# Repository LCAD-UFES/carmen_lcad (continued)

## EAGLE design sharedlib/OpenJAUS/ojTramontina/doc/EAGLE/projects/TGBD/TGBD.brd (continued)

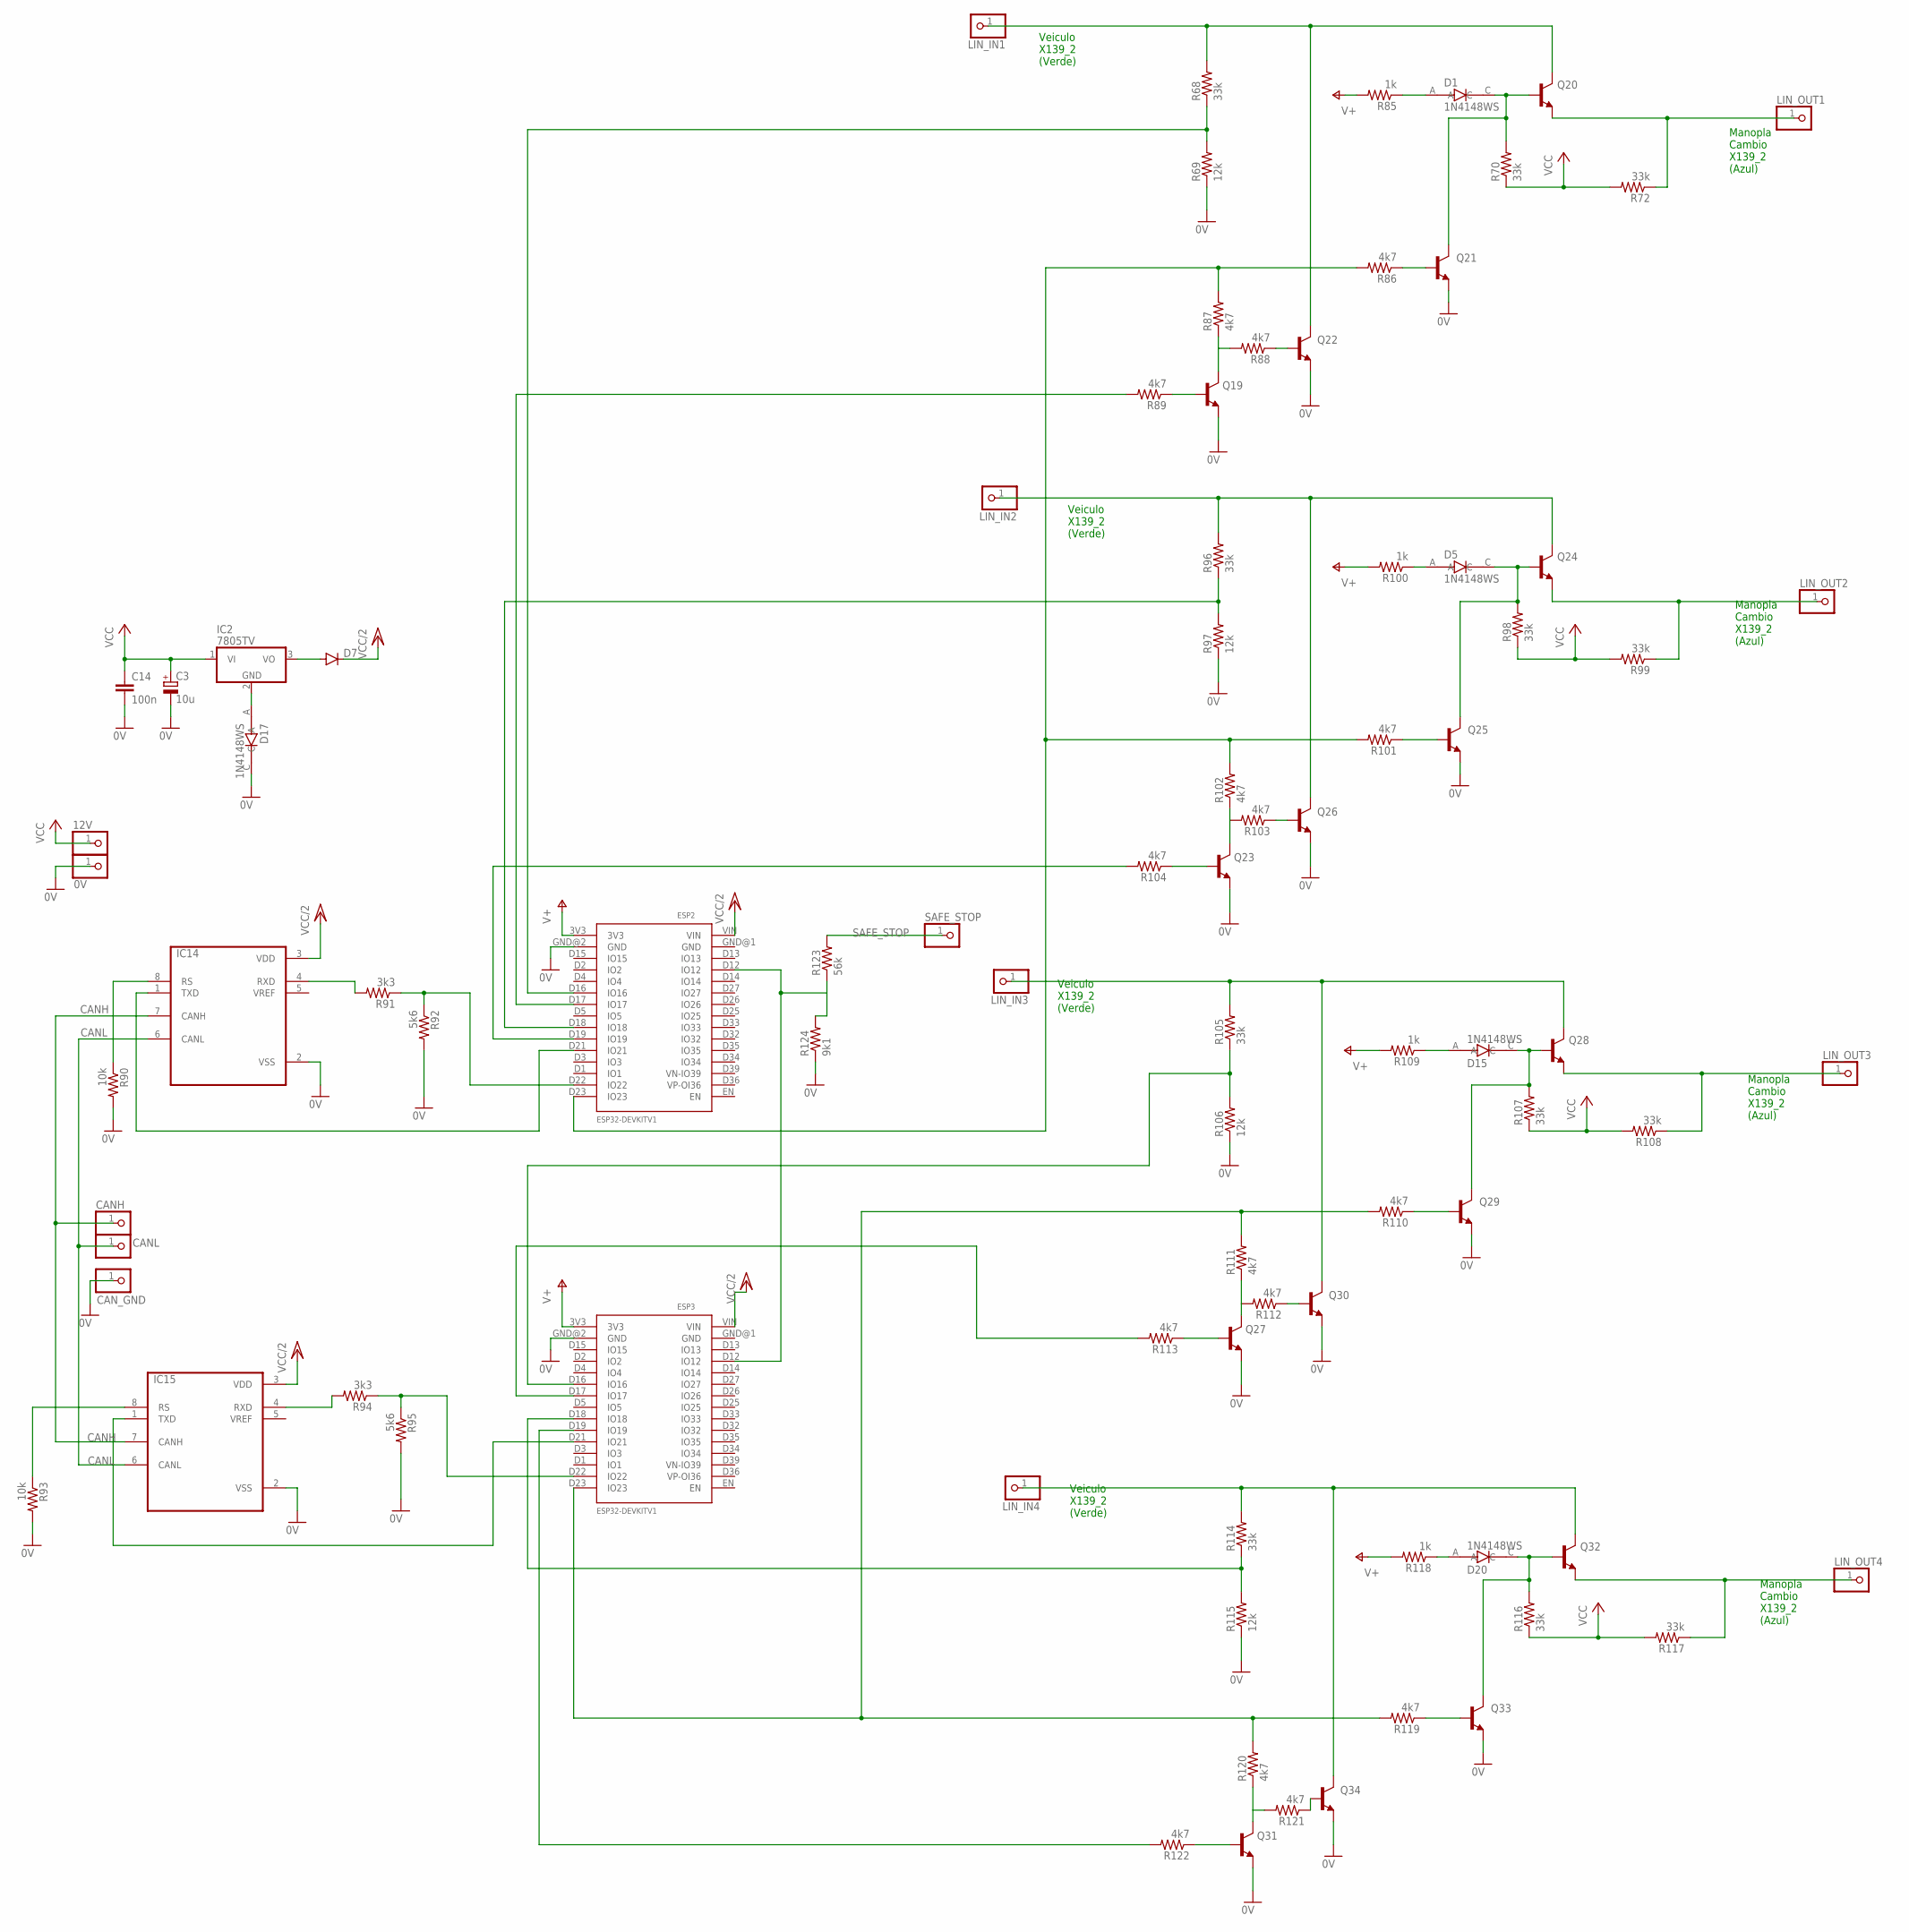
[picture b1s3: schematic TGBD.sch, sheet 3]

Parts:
0V, 12V: PINHD-1X1; 1X01
C3: 10u; A/3216-18R
C14: 100n; C0402
CANH: PINHD-1X1; 1X01
CANL: PINHD-1X1; 1X01
CAN_GND: PINHD-1X1; 1X01
D1, D5, D15, D17, D20: 1N4148WS; SODFL2512X100N
D7: DIODE-SOD123; SOD123
ESP2, ESP3: ESP32DEVKITV1; ESP32-DEVKITV1
IC2: 7805TV; TO220V
IC14, IC15: MCP2551-I/SN; SOIC127P599X175-8N
LIN_IN1, LIN_IN2, LIN_IN3, LIN_IN4: PINHD-1X1; 1X01
LIN_OUT1, LIN_OUT2, LIN_OUT3, LIN_OUT4: PINHD-1X1; 1X01
Q19, Q20, Q21, Q22, Q23, Q24, Q25, Q26, Q27, Q28, Q29, Q30, Q31, Q32, Q33, Q34: -NPN-TO92; TO92
R68, R70, R72, R96, R98, R99, R105, R107, R108, R114, R116, R117: 33k; R0402
R69, R97, R106, R115: 12k; R0603
R85, R100, R109, R118: 1k; R0402
R86, R87, R88, R89, R101, R102, R103, R104, R110, R111, R112, R113, R119, R120, R121, R122: 4k7; R0402
R90, R93: 10k; R0603
R91, R94: 3k3; R0402
R92, R95: 5k6; R0603
R123: 56k; R0603
R124: 9k1; R0603
SAFE_STOP: PINHD-1X1; 1X01

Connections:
0V: 0V.1, C3.-, C14.2, CAN_GND.1, D17.C, ESP2.GND@2 (GND), ESP3.GND@2 (GND), IC14.2 (VSS), IC15.2 (VSS), Q19.1 (E), Q21.1 (E), Q22.1 (E), Q23.1 (E), Q25.1 (E), Q26.1 (E), Q27.1 (E), Q29.1 (E), Q30.1 (E), Q31.1 (E), Q33.1 (E), Q34.1 (E), R69.1, R90.2, R92.2, R93.2, R95.2, R97.1, R106.1, R115.1, R124.1
CANH: CANH.1, IC14.7 (CANH), IC15.7 (CANH)
CANL: CANL.1, IC14.6 (CANL), IC15.6 (CANL)
unnamed: D1.C, Q20.2 (B), Q21.3 (C), R70.2
unnamed: D20.A, R118.1
unnamed: Q21.2 (B), R86.1
unnamed: Q19.3 (C), R87.1, R88.2
unnamed: Q22.2 (B), R88.1
unnamed: Q19.2 (B), R89.1
unnamed: D17.A, IC2.2 (GND)
unnamed: D7.A, IC2.3 (VO)
unnamed: IC14.8 (RS), R90.1
unnamed: IC14.4 (RXD), R91.2
unnamed: IC15.8 (RS), R93.1
unnamed: D15.A, R109.1
unnamed: D5.C, Q24.2 (B), Q25.3 (C), R98.2
unnamed: D5.A, R100.1
unnamed: Q25.2 (B), R101.1
unnamed: Q23.3 (C), R102.1, R103.2
unnamed: Q26.2 (B), R103.1
unnamed: Q23.2 (B), R104.1
unnamed: D15.C, Q28.2 (B), Q29.3 (C), R107.2
unnamed: D1.A, R85.1
unnamed: Q29.2 (B), R110.1
unnamed: Q27.3 (C), R111.1, R112.2
unnamed: Q30.2 (B), R112.1
unnamed: Q27.2 (B), R113.1
unnamed: LIN_OUT1.1, Q20.1 (E), R72.1
unnamed: LIN_OUT3.1, Q28.1 (E), R108.1
unnamed: D20.C, Q32.2 (B), Q33.3 (C), R116.2
unnamed: ESP2.D16 (IO16), R68.1, R69.2
unnamed: Q33.2 (B), R119.1
unnamed: Q31.3 (C), R120.1, R121.2
unnamed: Q34.2 (B), R121.1
unnamed: Q31.2 (B), R122.1
unnamed: LIN_OUT2.1, Q24.1 (E), R99.1
unnamed: ESP2.D12 (IO12), ESP3.D12 (IO12), R123.1, R124.2
unnamed: IC15.4 (RXD), R94.2
unnamed: ESP2.D17 (IO17), R89.2
unnamed: ESP2.D18 (IO18), R96.1, R97.2
unnamed: ESP2.D19 (IO19), R104.2
unnamed: ESP3.D16 (IO16), R105.1, R106.2
unnamed: ESP3.D17 (IO17), R113.2
unnamed: ESP3.D18 (IO18), R114.1, R115.2
unnamed: ESP3.D19 (IO19), R122.2
unnamed: LIN_OUT4.1, Q32.1 (E), R117.1
unnamed: ESP2.D22 (IO22), R91.1, R92.1
unnamed: ESP2.D23 (IO23), R86.2, R87.2, R101.2, R102.2
unnamed: ESP3.D23 (IO23), R110.2, R111.2, R119.2, R120.2
unnamed: ESP2.D21 (IO21), IC14.1 (TXD)
unnamed: ESP3.D22 (IO22), R94.1, R95.1
unnamed: ESP3.D21 (IO21), IC15.1 (TXD)
unnamed: LIN_IN1.1, Q20.3 (C), Q22.3 (C), R68.2
unnamed: LIN_IN2.1, Q24.3 (C), Q26.3 (C), R96.2
unnamed: LIN_IN3.1, Q28.3 (C), Q30.3 (C), R105.2
unnamed: LIN_IN4.1, Q32.3 (C), Q34.3 (C), R114.2
SAFE_STOP: R123.2, SAFE_STOP.1
V+: ESP2.3V3, ESP3.3V3, R85.2, R100.2, R109.2, R118.2; also elsewhere on the board
VCC: 12V.1, C3.+, C14.1, IC2.1 (VI), R70.1, R72.2, R98.1, R99.2, R107.1, R108.2, R116.1, R117.2
VCC/2: D7.C, ESP2.VIN, ESP3.VIN, IC14.3 (VDD), IC15.3 (VDD)

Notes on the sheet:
Manopla Cambio X139_2 (Azul)
Veiculo X139_2 (Verde)

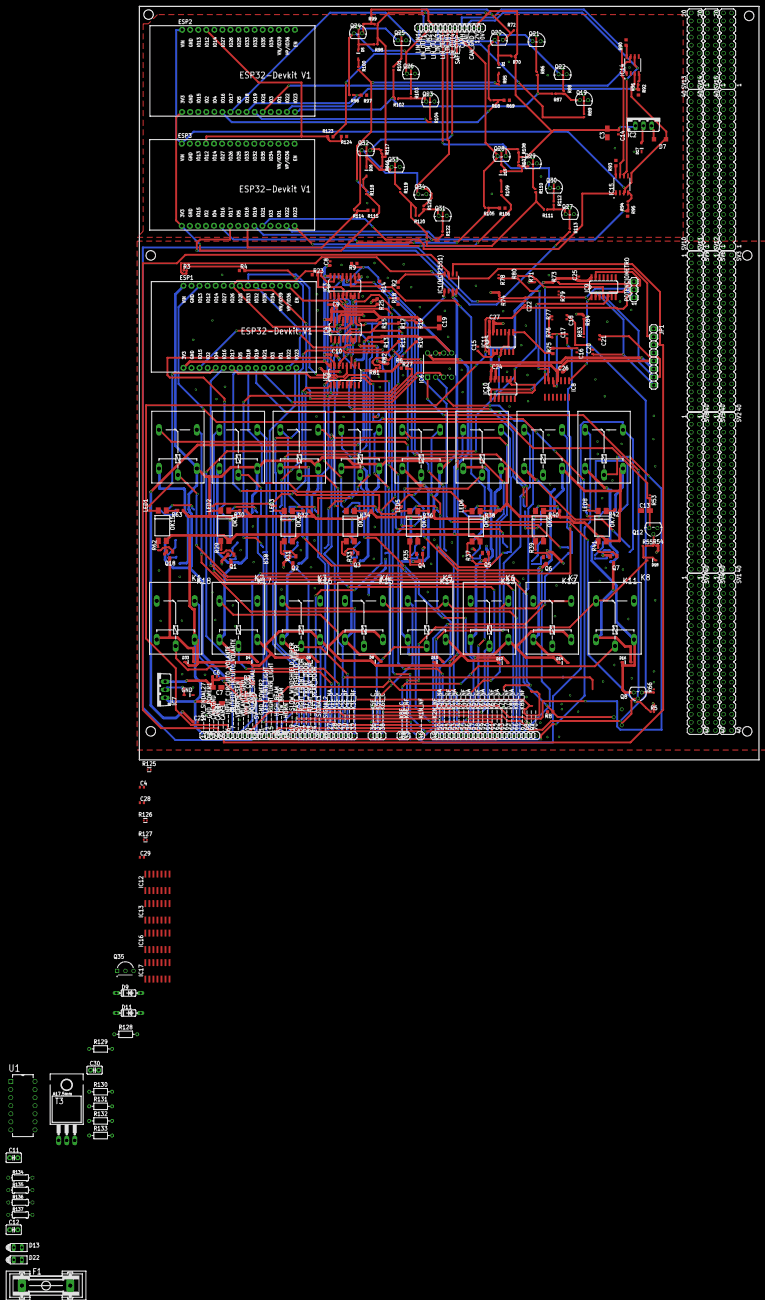
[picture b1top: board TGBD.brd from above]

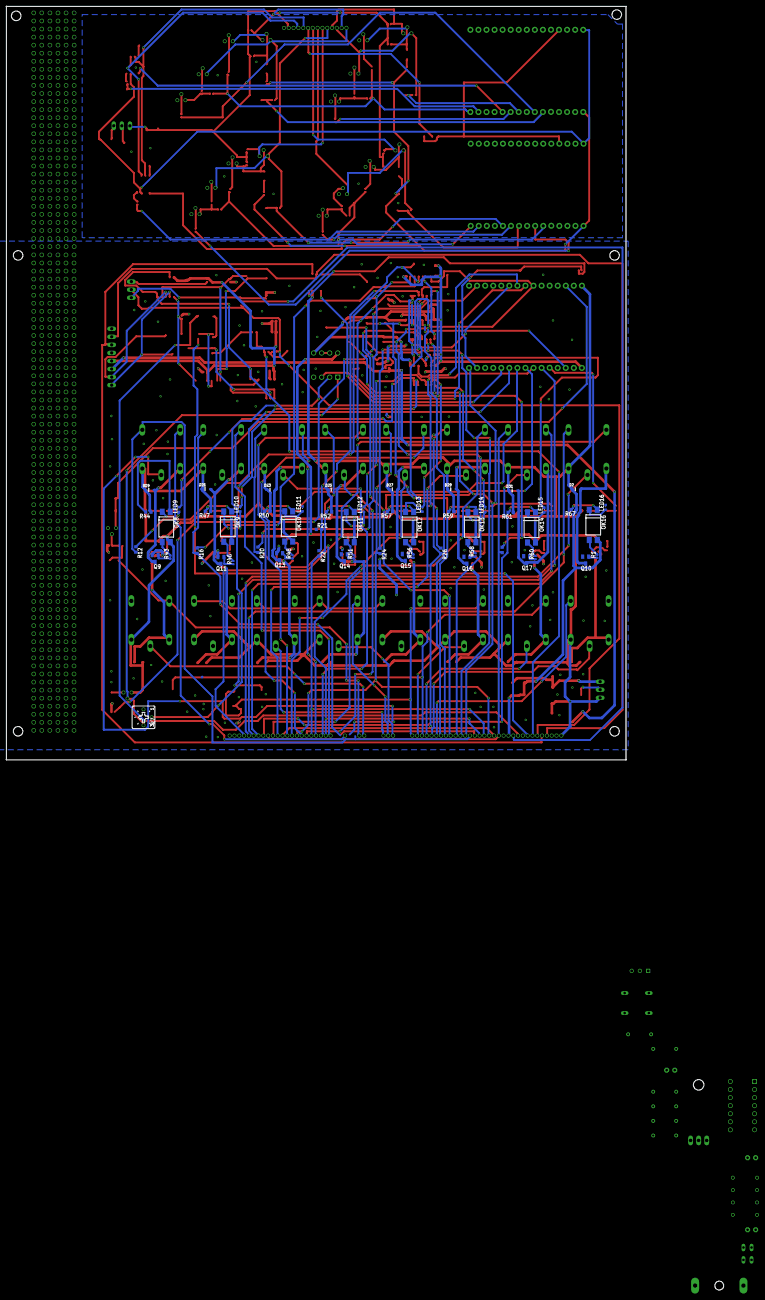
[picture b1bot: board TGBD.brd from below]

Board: 2 copper layers, 195.3 x 237.5 mm, 387 parts (57 on the bottom side), 261 nets.

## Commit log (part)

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2024-07-03 Odometry tests Hercules
2024-07-03 Visualize steering Hercules
2024-07-03 Updating steering visualization Hercules
2024-07-09 Steering Measurement Hercules
2024-07-09 Correcao do codigo de teste de angulo do Hercules
2024-07-09 Lume Mission
2024-07-09 Atualizacao de parametros e process do Hercules
2024-07-11 Adicionando parametros publish_gps
2024-07-11 Adicionando parâmetros publish_gps
2024-07-12 Calibracao de odometria Hercules
2024-07-22 subindo codigo do esp com a build
2024-07-22 removendo a build do esp , e subindo as alteracoes do hercules
2024-07-22 Adicionando controle do Steering Angle via can + build
2024-07-22 adicionando can para o esp
2024-07-25 Atualizacao de Parametros e Controle do Hercules
2024-08-05 PID hercules totalmente proporcional
2024-08-06 adicionando argumento para acionar RVIZ do process
2024-08-14 atulizacao process e missao
2024-08-14 Mensagem do commit
2024-08-19 correcao do codigo do esp
2024-08-19 subindo mudancas no PID atrasadas
2024-08-29 Adicao de funcionalidades para funcionar o Argos com o ojTorc
2024-09-03 subindo mudanças da apresentação
2024-09-04 utilizacao do novo mapa
2024-09-10 tudo pronto para a visita da ArcelorMittal
2024-09-12 Update readme.md - 0.00 meaning no translations
2024-09-12 Update readme.md - 0.00 meaning no rotations
2024-09-12 Argos Lidar initial code
2024-09-12 atualizacao da pose da missao
2024-09-14 melhorias no NMP
2024-09-17 melhorias para a missao de corredor do Hercules
2024-09-18 criacao da missao do corredor
2024-09-18 Argos lidar
2024-09-19 Modificacoes argos_lidar
2024-10-04 Alteracao do task manager e modificacao de parametros
2024-10-04 mission e process usando yolo
2024-10-07 Avanco lidar argos
2024-10-07 Avancos task manager
2024-10-08 Subindo grafo e outras coisas
2024-10-10 Adicao do map_ct13_hercules_lcad4_20240918
2024-10-11 Atualizar posicao caminhao hercules
2024-10-11 Adicionando modificacoes no Argos Lidar
2024-10-14 corrigindo conversao para esférica
2024-10-16 subindo mudancas do argos
2024-10-16 ajustes de parametros
2024-10-16 subindo process
2024-10-16 mudancao no argos playback.ini
2024-10-16 remocao de bug no viewer_3D
2024-10-17 Alterando parametros de Visualizacao Viewer e Argos_lidar do Argos
2024-10-23 renomeando process hercules e mudancas no lidar do argos
2024-10-24 subindo process hercules com nomes novos
2024-10-24 subindo binario do fastslam
2024-10-24 correcao
2024-10-24 adicionando binario correto
2024-10-24 subindo mudancas hercules
2024-10-24 subindo process fastslam argos
2024-10-24 subindo arquivos do argos
2024-10-24 subindo modelo 3d do argos comprimido
2024-10-25 subindo mudancas nos process
2024-10-25 pequenas mudacas process hercules playback
2024-10-25 correcao process argos playback
2024-11-13 mudancas process ct de portas abertas e killros
2024-11-28 consertando process da volta ufes
2024-11-28 comecando a desenvolver o conversor de mapa ROS/Carmen
2024-11-28 teste compilando
2025-01-06 colocando ojTorc para funcionar com webrtc
2025-01-09 pose global do argos funcionando
2025-01-13 configurando process playback webrtc
2025-01-13 argos global pos funcionando
2025-01-22 corrigindo escrita no argos.ini
2025-01-27 envio de odometria para o carmen
2025-01-28 publicando globalpos e trabalho com mapa
2025-02-06 correcao mapa e global_pos
2025-02-12 subindo process argos
2025-02-12 subindo pose global
2025-02-25 criacao ipc_watcher
    descobrindo msgs e subscribers
2025-02-25 subindo ipc_watcher
2025-02-25 inicio mapper
2025-02-25 trabalhando no argos_Ros_mapper
2025-03-06 preprando para mexer no mapper
2025-03-06 subindo correcoes codigo globalpos
2025-03-08 melhorias no modo navigate do Argos
2025-03-10 subindo modelo do go1
2025-03-10 adicao de mecanismos de simulacao do Unitree Go1
2025-03-25 inclusao de codigo no navigator_gui2 para salvar poses.txt para o relatorio para a ArcelorMittal
2025-03-25 codigo commitado que estava no laptop do Argos
2025-03-25 inclusao da versao do LiDAR Ouster do Lcad e ajuste do process argos/process-argos-lcad4-webrtc.ini e do ini argos/carmen-argos.ini para usa-lo
2025-03-26 preparacao para viewer3D receber xyz_pointcloud
2025-03-27 avancos viewer3D
2025-03-27 XYZ pointcloud lidar
2025-03-30 Melhorias para compilar em Jetsons (Argos)
2025-03-31 corrigindo makefiles para visualizacao xyz_pointcloud no viewer 3d
2025-04-02 carmen rodando no Argos
2025-04-03 argos params update
2025-04-04 subindo parametros ouster
2025-04-04 corrigindo odometria do argos
2025-04-07 update ojArgos
2025-04-07 subindo process argos da jetson
2025-04-08 update medida de angulo
2025-04-09 subindo camera_drivers
2025-04-09 melhoras no Argos, PID, etc.
2025-04-09 subindo process-argos-playback.ini
2025-04-09 ajuste da parametros para o argos playback ficar bom
2025-04-10 melhorias no argos para ele ficar quase andando autonomo
2025-04-10 primeiro mapa do corredor todo com o Argos
2025-04-10 primeiro mapa feito pelo Argos!
2025-04-11 ajustando PID
2025-04-11 adicao de grafo para o Argos
2025-04-15 melhorias odometria e controle argos
2025-04-15 trocando drivers do argos para cpp
2025-04-15 fix fastslam and road_network_generator type
2025-04-15 Update gitignore
2025-04-15 Camera viewer and camera driver
2025-04-15 Adicionando novo grafo para o Argos corredor CT13
2025-04-15 Process de calibracao de odometria do argos
2025-04-16 Camera driver atualizado para usar menos memória
2025-04-16 Adicionando novos modulos no kill_ros
2025-04-16 Adicionando new_graph
2025-04-16 Remove submodule src/camera_drivers
2025-04-16 Camera drivers fonte
2025-04-16 road_network_generator
2025-04-16 Adicionando argos road network generator
2025-04-16 criando grafo de volta
2025-04-16 dados teste arcelor
2025-04-17 Limpando o mapa do argos
2025-04-22 subindo teste para arcelor
2025-04-22 subindo navigate argos
2025-04-22 subindo resultados do teste do argos da arcelor
2025-04-24 adicionando destruturores para drawers xyz_pointcloud
2025-04-29 incorporando messagem xyz_pointcloud dentro do módulo do viewer
2025-04-29 corrigindo ip do ouster
2025-04-29 update process para teste com caixas
2025-04-29 update process fastslam e playback argos
2025-05-06 melhorias para o controle pelo joystick
2025-05-14 subindo anotacoes argos
2025-05-19 Criando a pasta do prometheus
2025-05-19 subindo mapa do argos ate honofre
2025-05-26 posicao do honofre no rddf
2025-05-26 subindo grafo ate o honofre
2025-05-27 adicionando link para download do log
2025-06-06 adicionando mais documentações ao carmen
2025-06-06 update fastslam argos para arcelor
2025-06-06 update doc Carmen
2025-06-13 subindo codigos do Hercules que estavam apenas localmente
2025-06-17 adicionando sleep ao ouster para consertar erro
2025-06-24 subindo correcao do Ouster
2025-06-30 ajustando ojPrometheus
2025-07-01 atualizando process do prometheus
2025-07-01 Update ipc_watcher
2025-07-02 update ipc_watcher - adicionando update dos timers
2025-07-14 Revert "atualizando process do prometheus"
    This reverts commit 3b0afcde173827ba11f10c81894f7756bc17e918.
2025-07-22 subindo mudancas de config
2025-07-24 update params argos para mapa grid_res 5cm size 21m
2025-07-24 Adicionando tutorial de como verificar problema de falta de processamento
2025-07-24 corrigindo param de lidar
2025-07-25 update Makefile
2025-07-29 subindo codigo inicial para o viewer gerar arquivo ply
2025-07-29 ajustando param de lidar
2025-08-11 adicionando funcao de log compact map
2025-08-20 update parametros do argos
2025-08-21 update arquivos Hercules
2025-08-21 adicionando process hercules
2025-08-21 mudando process para espaco empreendedor
2025-08-28 missao de pegar e entregar bloco no espaco empreendedor para teste
2025-09-05 correcao no Makefile geral
2025-09-05 melhorias em hercules/process-hercules-navigate.ini
2025-09-15 update README fordescape para plotar curvas
2025-09-15 update process argos
2025-09-17 retirando log de compact map
2025-09-17 subindo print_ipc_message
2025-09-23 Drivers do Prometheus compilando
2025-09-23 consertando Makefile do Prometheus
2025-09-24 README para a instalação do SDK
2025-09-24 corrigido frequencia do CAN no prometheu
2025-09-26 Process prometheus atualizado
2025-09-30 atualizando modulo do prometheus
2025-10-06 atualizando parametros do prometheus
2025-11-07 adicionando parametros para lidar hesai
2025-11-07 adicionando process para teste do hesai
2025-11-11 adicionando hesai para uso principal do argos
2025-11-11 Alterei os arquivos process-navigate-volta-da-ufes-pid.ini e process-volta_da_ufes_playback_viewer_3D.ini para apontarem para o mapa map_voltadaufes-201903025 e para o log log_volta_da_ufes_20230422-1
2025-11-13 subindo parametros argos
2025-11-14 reduzindo steering delay argos
2025-12-03 update parametros argos
2025-12-30 adding prometheus obj
2025-12-30 atualizando prometheus
2026-01-11 Ajustando parametros para o Prometheus
2026-01-11 removendo define duplicado
2026-01-11 removendo caracteres que não sejam ASCII
2026-01-11 adicionando process pid para o Prometheus
2026-01-11 executaveis do prometheus no process
2026-01-14 Prometheus funcionando, precisando de ajustes na temporizacao e de filtro/PID
2026-01-14 alteracoes prometheus
2026-01-15 melhorando mensagem de erro e direcionando o usuario para o readme correto
2026-01-18 adicionando process fastslam para o prometheus
2026-01-21 process navigate prometheus corrigido
2026-01-22 adicionando flag de log de dados de sensores de odometria para o prometheus
2026-01-22 corrigindo codigo do prometheus, e flag '--log_sensor_data' funcionando
2026-01-22 adicionando mapa, rddf e grafo do prometheus
2026-02-26 subindo mudancas argos indo ao honofre autonomo
2026-03-02 subindo codigo de calculo de RMSE de navegacao
2026-03-09 rddf_by_road_map_image (unfinished)
2026-03-10 rddf_by_road_map_image (unfinished#2)
2026-03-10 rddf_by_road_map_image (unfinished#3)
2026-03-11 rddf_by_road_map_image (unfinished#4)
2026-03-11 rddf_by_road_map_image (unfinished#5)
2026-03-11 adicionando bridge para ros_carmen
2026-03-11 correcao README ros_bridge
2026-03-13 rddf_by_road_map_image (unfinished#6)
2026-03-25 ajustando parametros e process para rodar simulado em espaco apertado
2026-04-23 adicionando mudancas para o argos arcelor, corrigindo desenho do mapa
2026-04-24 carmen ini do argos
2026-04-24 estado no laptop
2026-04-24 mapa para o argos
2026-04-24 subindo process autonomo argos e colisao
2026-04-24 process argos
2026-04-24 mapa e grafo argos
2026-04-27 subindo param argos para mapa arcelor e inicio de update mapper para angulo range_max_factor customisavel
2026-04-27 adicionando mapa do argos, e parametro mapper para aplicar range_max_factor
2026-04-29 mapa argos arcelor 2026-04-29-1
2026-04-30 ajuste paramentos argos
2026-04-30 routa inicial falta ajusta
2026-04-30 subindo editor de grafo
2026-04-30 subindo mudancas argos para gerar mapa
2026-04-30 subindo grafo do argos na arcelor
2026-05-02 Update README.md to remove unnecessary comments
    Removed outdated remarks and questions from README.
2026-05-05 atualizando o xsens_argos
2026-05-06 configuração Localizer e logger
2026-05-07 map imu argos
2026-05-07 criando branch para teste imu localize
2026-05-07 preparando para merge do argos com update
2026-05-14 ajustei no imu
2026-05-14 mapa ate a copiadora honofre
2026-05-14 ajuste mapa
2026-05-18 ajuste no mapa
2026-05-18 ajsute dos param
2026-05-19 tirando os hardcode
2026-05-19 rddf e map argos com imu
2026-05-19 ajuste mapa holofre
2026-05-19 subindo grafo para ir ao honofre com imu
2026-05-19 Map Editor 2 - Editor de mapa completo
2026-05-19 corrigindo leitura de parametros localize para imu
2026-05-19 corrigindo alpha do imu argos
2026-05-21 padrão de organização novo
2026-05-27 rddf lcad4 loop
2026-06-02 subindo pendencias
2026-06-02 Ajuste do map e process com IMU
2026-06-02 limpando pasta do argos de arquivos antigos
2026-06-02 mais mudancas process argos
2026-06-02 subindo arquivo obj do argos
2026-06-02 ajustando parametros para fazer mapa
2026-06-08 atualizando o process playback
2026-06-08 ajustando threshhold para ruido imu
2026-06-11 subindo link para mapeditor2
2026-06-11 correcao link simbolico
2026-06-24 flag de hz do driver do imu
